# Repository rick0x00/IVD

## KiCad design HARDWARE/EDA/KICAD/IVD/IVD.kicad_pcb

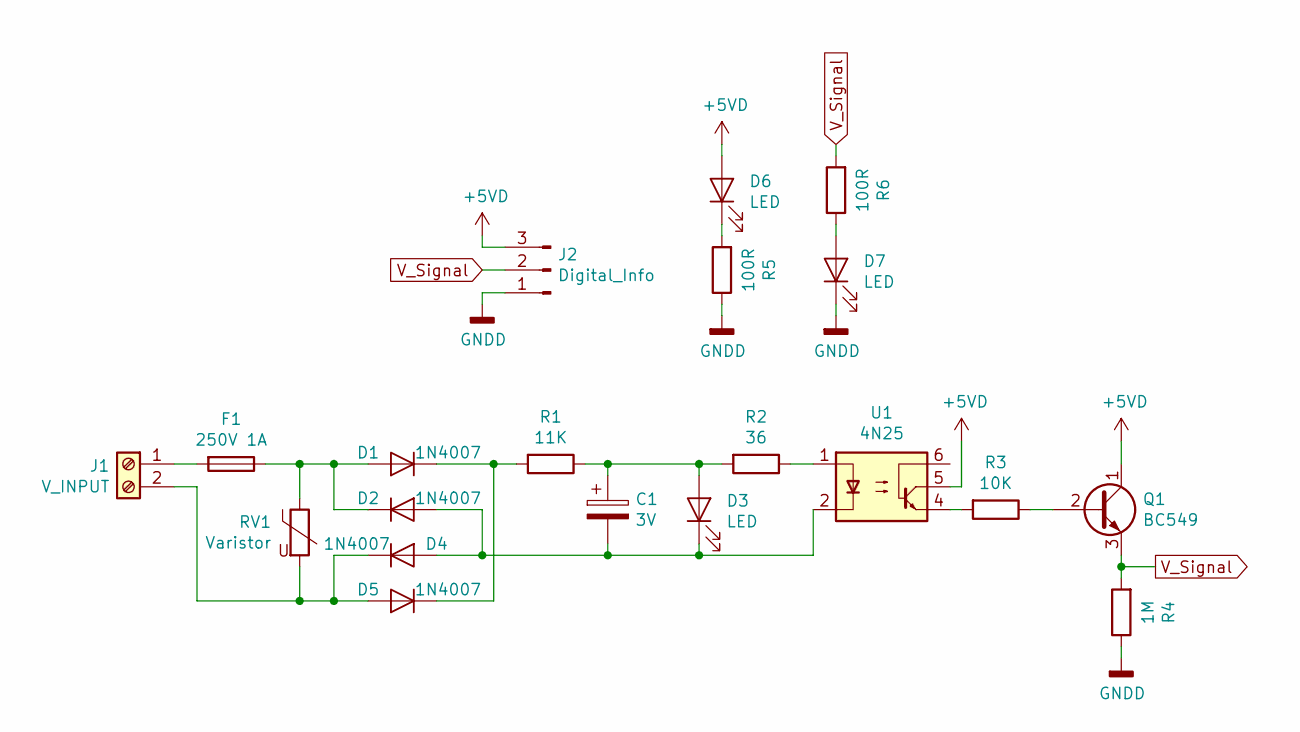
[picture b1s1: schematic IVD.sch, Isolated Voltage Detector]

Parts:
C1: 3V; CP_Radial_D10.0mm_P3.50mm
D1, D2, D4, D5: 1N4007; D_DO-41_SOD81_P10.16mm_Horizontal
D3: LED; LED_D5.0mm_Clear
D6: LED; LED_D5.0mm
D7: LED; LED_D5.0mm_IRGrey
F1: 250V 1A; Fuse_Blade_ATO_directSolder
J1: V_INPUT; PhoenixContact_GMSTBA_2,5_2-G_1x02_P7.50mm_Horizontal
J2: Digital_Info; PinHeader_1x03_P2.54mm_Horizontal
Q1: BC549; TO-92_Inline_Wide
R1: 11K; R_Axial_DIN0207_L6.3mm_D2.5mm_P7.62mm_Horizontal
R2: 36; R_Axial_DIN0207_L6.3mm_D2.5mm_P7.62mm_Horizontal
R3: 10K; R_Axial_DIN0207_L6.3mm_D2.5mm_P7.62mm_Horizontal
R4: 1M; R_Axial_DIN0207_L6.3mm_D2.5mm_P7.62mm_Horizontal
R5, R6: 100R; R_Axial_DIN0207_L6.3mm_D2.5mm_P7.62mm_Horizontal
RV1: Varistor; RV_Disc_D12mm_W4mm_P7.5mm
U1: 4N25; DIP-6_W7.62mm_LongPads

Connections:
+5VD: D6.2 (A), J2.3, Q1.1 (C), U1.5
GNDD: D7.1 (K), J2.1, R4.1, R5.1
unnamed: C1.1, D3.2 (A), R1.1, R2.2
unnamed: C1.2, D2.2 (A), D3.1 (K), D4.2 (A), U1.2
unnamed: D1.1 (K), D5.1 (K), R1.2
unnamed: D1.2 (A), D2.1 (K), F1.1, RV1.1
unnamed: D4.1 (K), D5.2 (A), J1.2, RV1.2
unnamed: D6.1 (K), R5.2
unnamed: D7.2 (A), R6.1
unnamed: F1.2, J1.1
unnamed: Q1.2 (B), R3.1
unnamed: R2.1, U1.1
unnamed: R3.2, U1.4
V_Signal: J2.2, Q1.3 (E), R4.2, R6.2

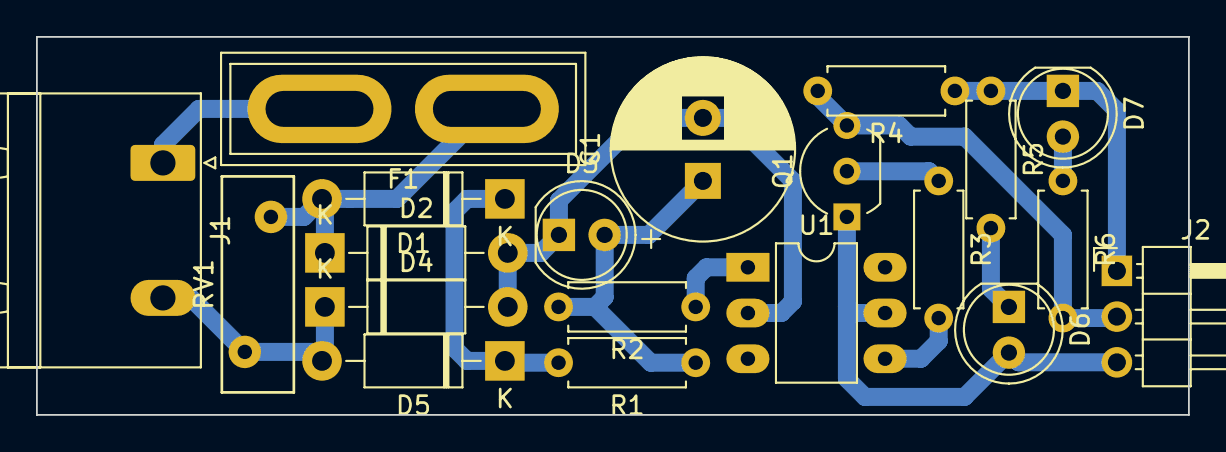
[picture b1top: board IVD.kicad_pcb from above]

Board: 2 copper layers, 64.0 x 21.0 mm, 20 parts (0 on the bottom side), 14 nets.

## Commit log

2021-10-26 ajust repository
2021-10-26 schematic finished
2021-10-26 PCB finished
2021-10-26 adjust PCB
2021-10-26 finished board
2021-10-27 add images
